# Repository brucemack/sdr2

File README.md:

Overview
========

This is a homebrew SDR rig with no dependency on external computers/soundcards/etc. 

Build/Debug Commands
====================

One-time setup of make process:

        git submodule update --init
        mkdir build
        cd build
        cmake -DPICO_BOARD=pico2 ..

Command used to flash code to board:        

        ~/git/openocd/src/openocd -s ~/git/openocd/tcl -f interface/cmsis-dap.cfg -f target/rp2350.cfg -c "adapter speed 5000" -c "rp2350.dap.core1 cortex_m reset_config sysresetreq" -c "program main.elf verify reset exit"

Pico 2 Pinout Notes
===================
```
GP0  - (Reserved for UART0 TX)
GP1  - (Reserved for UART0 RX)

GP2  - 
GP3  - 
GP4  - I2S SCK out to PCM1804 ADC and PCM5100 DAC
GP5  - RST out to PCM1804 ADC

GP6  - I2S DIN in from PC1804 ADC
GP7  - I2S BCK out to PC1804 ADC
GP8  - I2S LRCK out to PC1804 ADC
GP9  - I2S DOUT out to PCM5100 DAC

GP10 - I2S BCK out to PCM5100 DAC
GP11 - I2S LRCK out to PCM5100 DAC
GP12 - User button input 0
GP13 - User button input 1
GP14 - PTT input 
GP15 - 
GP16 - I2C0 SDA for Si5351 (Addr 0x60)
GP17 - I2C0 SCL for Si5351 (Addr 0x60)

GP18 - I2C1 SDA for display and IO expander
GP19 - I2C1 SCL for display and IO expander
GP20 - Rotary encoder I channel input
GP21 - Rotary encoder Q channel input

GP22 - 
GP26 - ADC0 for forward power
GP27 - ADC1 for reverse power
GP28 - 
```
IO Expander Notes
=================
```
P0 - User indicator LED output
P1 - Audio amplifier enable (Low=enable output, high=shutdown amplifier)
P2 - ADC Input Select (Low=Microphone preamp out, High=QSD channel out)
P3 - TX band select 0
P4 - TX band select 1
P5 - RX band select 0
P6 - RX band select 1
P7 - Transmit PA enable (active low)
```

Wiring Notes
============

* TXRX board I_PLUS (J4:1) -> Audio Breakout INL_PLUS (J4:1)
* TXRX board I_MINUS (J4:2) -> Audio Breakout INL_MINUS (J4:2)
* TXRX board Q_PLUS (J4:3) -> Audio Breakout INR_PLUS (J4:4)
* TXRX board Q_MINUS (J4:5) -> Audio Breakout INR_MINUS (J4:3)
* Microphone input is connected to the INL_PLUS/INL_MINUS pins on the audio breakout board.

Hardware Notes
==============

### Instrumentation Amplifiers on Receive Board

See Horowitz and Hill (3rd ed, section 5.16, figure 5.88) for a description of the 
instrumentation amplifier configuration used on the receive board.  Gain for this amplifier is 
controlled determined by 1 + 2 R<sub>f</sub> / R<sub>g</sub>.  Notice that the feedback 
path is tapped after a 47 ohm resistor to set the output impedance of the stage.

Assuming R<sub>f</sub> is 520, R<sub>g</sub> is 100, the theoretical gain is about 11.

### Random

dBm = 30 + 20 * log(Vrms/sqrt(Z0))

Research
========

Consider the PCM1863 ADC? 

Consider the TS5A4624 analog switch (logic high = 2.4V w/ 5V supply)

Consider PCF8574A IO expander: https://www.ti.com/lit/ds/symlink/pcf8574a.pdf?ts=1728869550852&ref_url=https%253A%252F%252Fwww.mouser.com%252F

RF Transistor: https://www.nxp.com/docs/en/data-sheet/BFU590G.pdf

References
==========

[PCM1804 Datasheet](https://www.ti.com/lit/ds/symlink/pcm1804.pdf)
[PCM5100 Datasheet](https://www.ti.com/lit/ds/symlink/pcm5102.pdf)

Steps to Build CMSIS-DSP
========================

The library gets built once in a parallel project:

        cd ~/pico
        mkdir CMSISDSP
        cd CMSISDSP
        git clone https://github.com/ARM-software/CMSIS-DSP.git        
        git clone https://github.com/ARM-software/CMSIS_6.git
        cp $PICO_SDK_PATH/external/pico_sdk_import.cmake .

Then setup the CMakeLists.txt shown below and build:

        mkdir build
        cd build
        # IMPORTANT! pico2 build enables the generation of FPU instructions
        cmake -DPICO_BOARD=pico2 ..
        make -j4

What the CMakeLists.txt looks like:

```
cmake_minimum_required (VERSION 3.6)

# Pull in Pico SDK (must be before project)
include(pico_sdk_import.cmake) 

set(HOME $ENV{HOME})
set(CMSISDSP ${HOME}/pico/CMSISDSP/CMSIS-DSP)
set(CMSISCORE ${HOME}/pico/CMSISDSP/CMSIS_6/CMSIS/Core)

# Define the project
project (cmsis-dsp VERSION 0.1)

# Initialise the Pico SDK
pico_sdk_init()

add_subdirectory(${CMSISDSP}/Source bin_dsp)

target_compile_options(CMSISDSP PUBLIC 
    -Wsign-compare
    -Wdouble-promotion
    -Ofast -ffast-math
    -DNDEBUG
    -Wall -Wextra  -Werror
    -fshort-enums 
    #-fshort-wchar
)
```

Example of referencing the built CMSIS-DSP library in a client project:

```
set(HOME $ENV{HOME})
target_include_directories(main PRIVATE
  ${HOME}/pico/CMSISDSP/CMSIS-DSP/Include
  ${HOME}/pico/CMSISDSP/CMSIS_6/CMSIS/Core/Include
)
target_link_libraries(main
  pico_stdlib
  ${HOME}/pico/CMSISDSP/build/bin_dsp/libCMSISDSP.a
)
```
License
=======

SDR2 Rig - Copyright (C) Bruce MacKinnon KC1FSZ, 2025

This program is free software: you can redistribute it and/or modify
it under the terms of the GNU General Public License as published by
the Free Software Foundation, either version 3 of the License, or
(at your option) any later version.

This program is distributed in the hope that it will be useful,
but WITHOUT ANY WARRANTY; without even the implied warranty of
MERCHANTABILITY or FITNESS FOR A PARTICULAR PURPOSE.  See the
GNU General Public License for more details.

You should have received a copy of the GNU General Public License
along with this program.  If not, see <https://www.gnu.org/licenses/>.

FOR AMATEUR RADIO USE ONLY.
NOT FOR COMMERCIAL USE WITHOUT PERMISSION.

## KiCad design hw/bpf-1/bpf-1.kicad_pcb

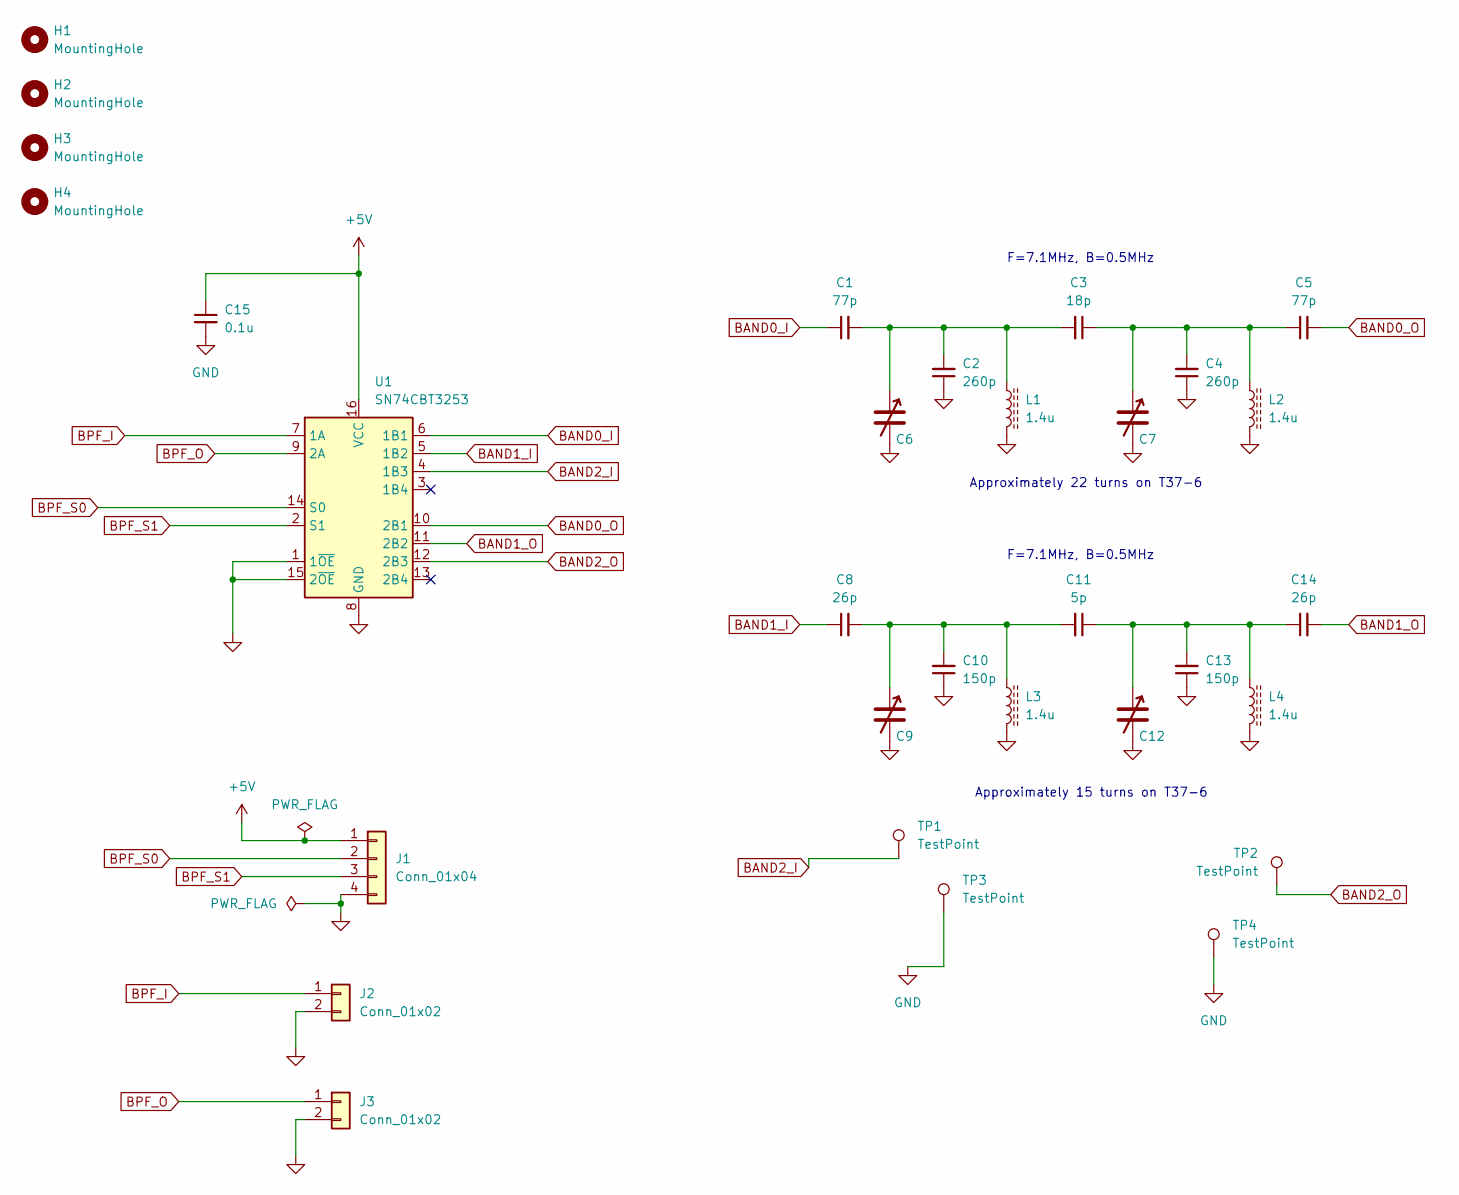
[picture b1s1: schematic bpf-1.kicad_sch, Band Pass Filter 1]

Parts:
C1, C5: 77p; C_0805_2012Metric_HandSolder
C2, C4: 260p; C_0805_2012Metric_HandSolder
C3: 18p; C_0805_2012Metric_HandSolder
C6, C7, C9, C12: C_Variable; VCAP_GKG30086-05_SGM-L
C8, C14: 26p; C_0805_2012Metric_HandSolder
C10, C13: 150p; C_0805_2012Metric_HandSolder
C11: 5p; C_0805_2012Metric_HandSolder
C15: 0.1u; C_0805_2012Metric_HandSolder
H1, H2, H3, H4: MountingHole; MountingHole_3.5mm
J1: Conn_01x04; PinHeader_1x04_P2.54mm_Vertical
J2, J3: Conn_01x02; PinHeader_1x02_P2.54mm_Vertical
L1, L2, L3, L4: 1.4u; FT37-43 Unifilar
TP1, TP2, TP3, TP4: TestPoint; TestPoint_Pad_1.5x1.5mm
U1: SN74CBT3253; SOIC-16_3.9x9.9mm_P1.27mm

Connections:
+5V: C15.1, J1.1, U1.16 (VCC)
BAND0_I: C1.1, U1.6 (1B1)
BAND0_O: C5.2, U1.10 (2B1)
BAND1_I: C8.1, U1.5 (1B2)
BAND1_O: C14.2, U1.11 (2B2)
BAND2_I: TP1.1, U1.4 (1B3)
BAND2_O: TP2.1, U1.12 (2B3)
BPF_I: J2.1, U1.7 (1A)
BPF_O: J3.1, U1.9 (2A)
BPF_S0: J1.2, U1.14 (S0)
BPF_S1: J1.3, U1.2 (S1)
GND: C2.1, C4.1, C6.2, C7.2, C9.2, C10.1, C12.2, C13.1, C15.2, J1.4, J2.2, J3.2, L1.2, L2.2, L3.2, L4.2, TP3.1, TP4.1, U1.1 (1~OE), U1.8 (GND), U1.15 (2~OE)
unnamed: C1.2, C2.2, C3.2, C6.1, L1.1
unnamed: C3.1, C4.2, C5.1, C7.1, L2.1
unnamed: C8.2, C9.1, C10.2, C11.2, L3.1
unnamed: C11.1, C12.1, C13.2, C14.1, L4.1

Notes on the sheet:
F=7.1MHz, B=0.5MHz
Approximately 15 turns on T37-6
Approximately 22 turns on T37-6

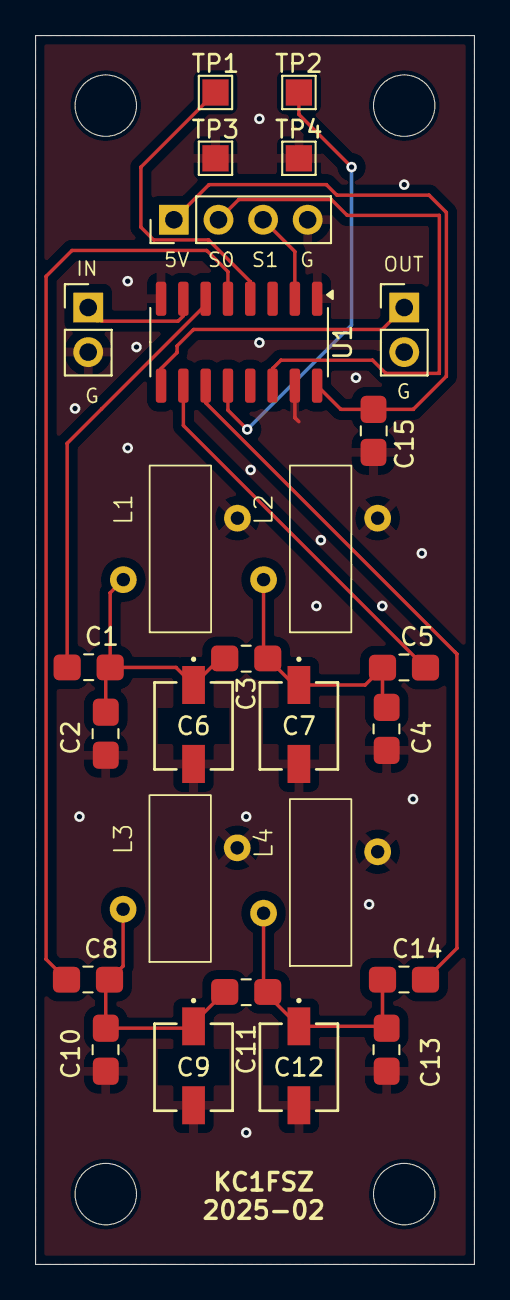
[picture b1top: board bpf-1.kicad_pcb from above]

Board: 2 copper layers, 25.0 x 70.0 mm, 31 parts (0 on the bottom side), 16 nets.

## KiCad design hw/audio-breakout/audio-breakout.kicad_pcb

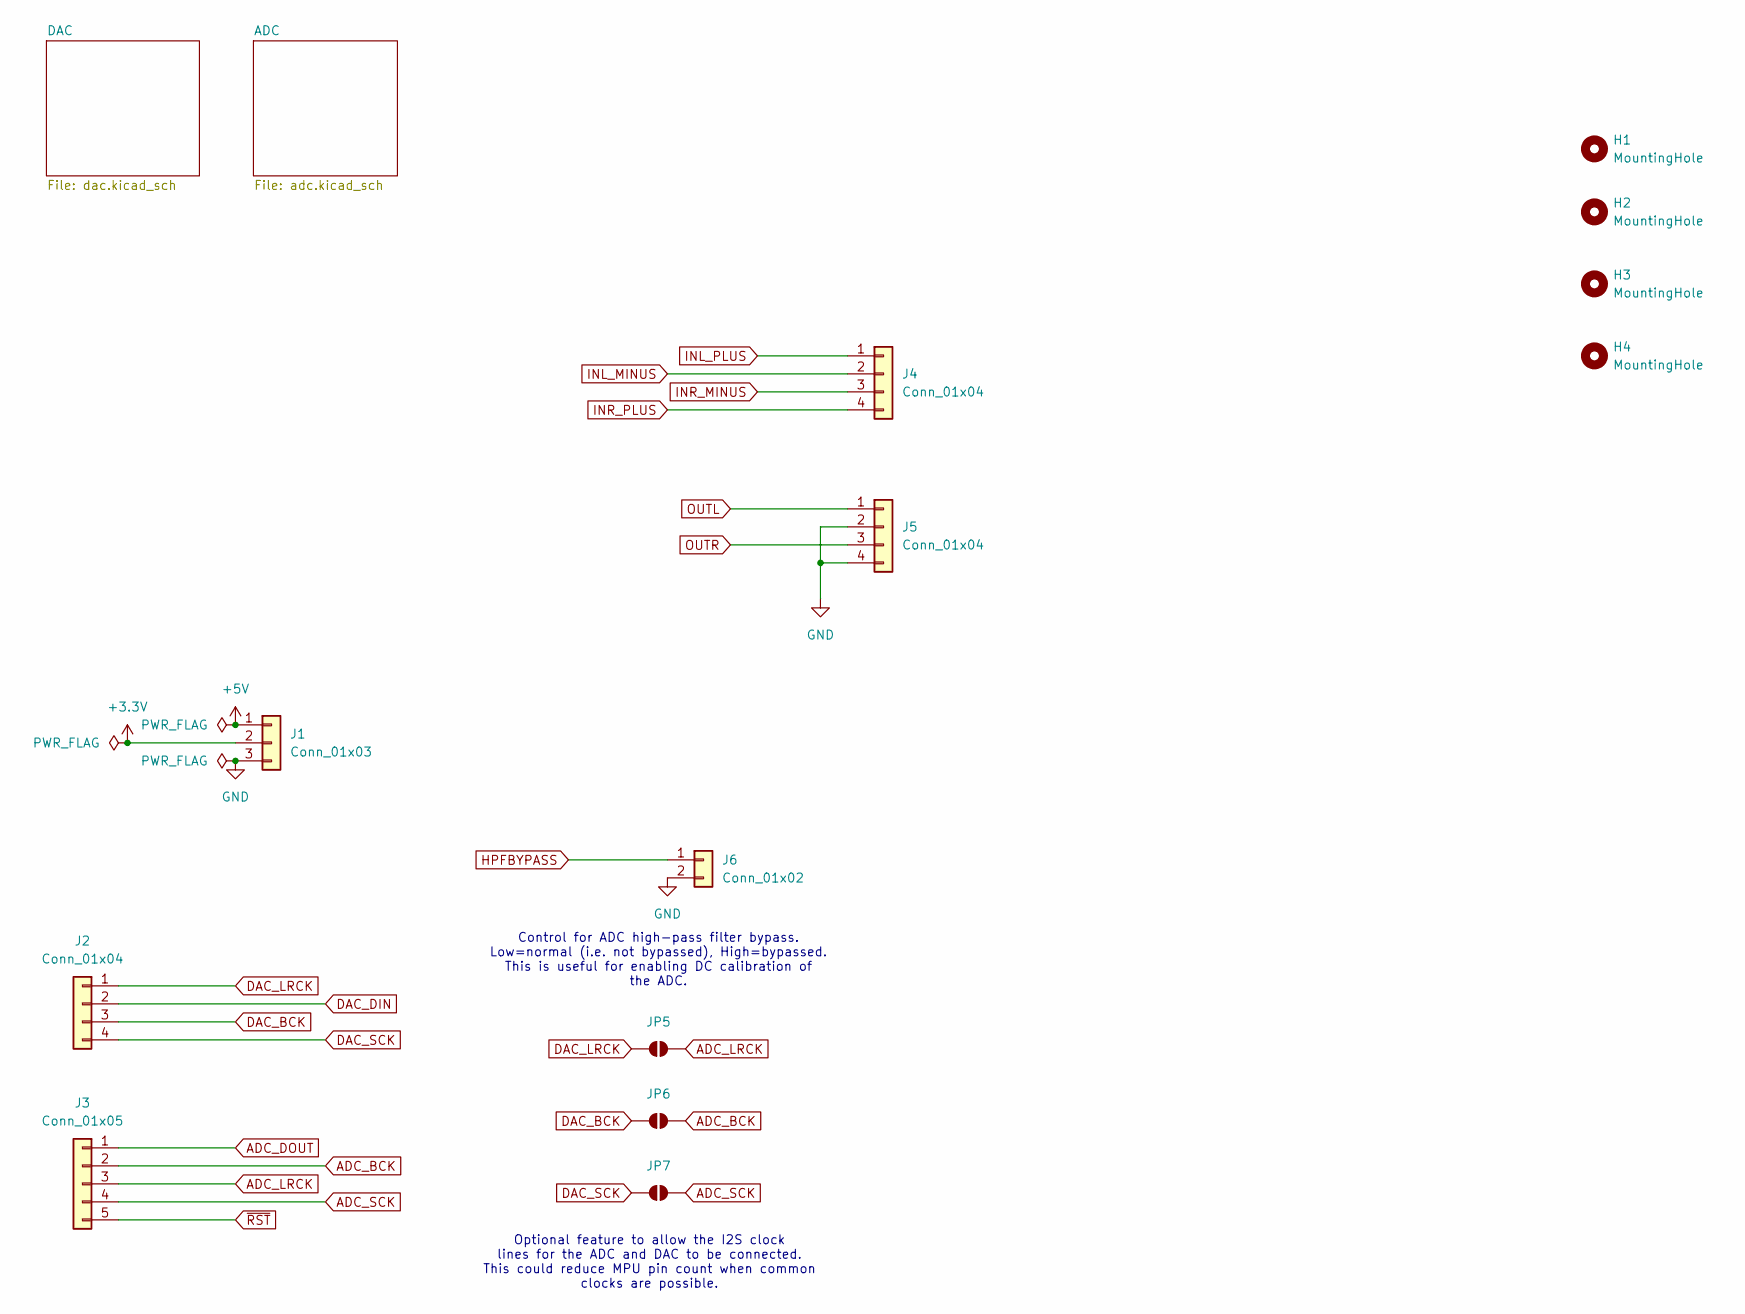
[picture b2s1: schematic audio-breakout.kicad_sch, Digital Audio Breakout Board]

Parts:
H1, H2, H3, H4: MountingHole; MountingHole_3.5mm
J1: Conn_01x03; PinSocket_1x03_P2.54mm_Vertical
J2: Conn_01x04; PinSocket_1x04_P2.54mm_Vertical
J3: Conn_01x05; PinSocket_1x05_P2.54mm_Vertical
J4, J5: Conn_01x04; PinHeader_1x04_P2.54mm_Vertical
J6: Conn_01x02
JP5, JP6, JP7: SolderJumper_2_Open; SolderJumper-2_P1.3mm_Open_Pad1.0x1.5mm

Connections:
+3.3V: J1.2; also elsewhere on the board
+5V: J1.1; also elsewhere on the board
ADC_BCK: J3.2, JP6.2 (B); also elsewhere on the board
ADC_DOUT: J3.1; also elsewhere on the board
ADC_LRCK: J3.3, JP5.2 (B); also elsewhere on the board
ADC_SCK: J3.4, JP7.2 (B); also elsewhere on the board
DAC_BCK: J2.3, JP6.1 (A); also elsewhere on the board
DAC_DIN: J2.2; also elsewhere on the board
DAC_LRCK: J2.1, JP5.1 (A); also elsewhere on the board
DAC_SCK: J2.4, JP7.1 (A); also elsewhere on the board
INL_MINUS: J4.2; also elsewhere on the board
INL_PLUS: J4.1; also elsewhere on the board
INR_MINUS: J4.3; also elsewhere on the board
INR_PLUS: J4.4; also elsewhere on the board
OUTL: J5.1; also elsewhere on the board
OUTR: J5.3; also elsewhere on the board
~RST: J3.5; also elsewhere on the board

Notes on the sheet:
Optional feature to allow the I2S clock lines for the ADC and DAC to be connected. This could reduce MPU pin count when common clocks are possible.
Control for ADC high-pass filter bypass. Low=normal (i.e. not bypassed), High=bypassed. This is useful for enabling DC calibration of the ADC.

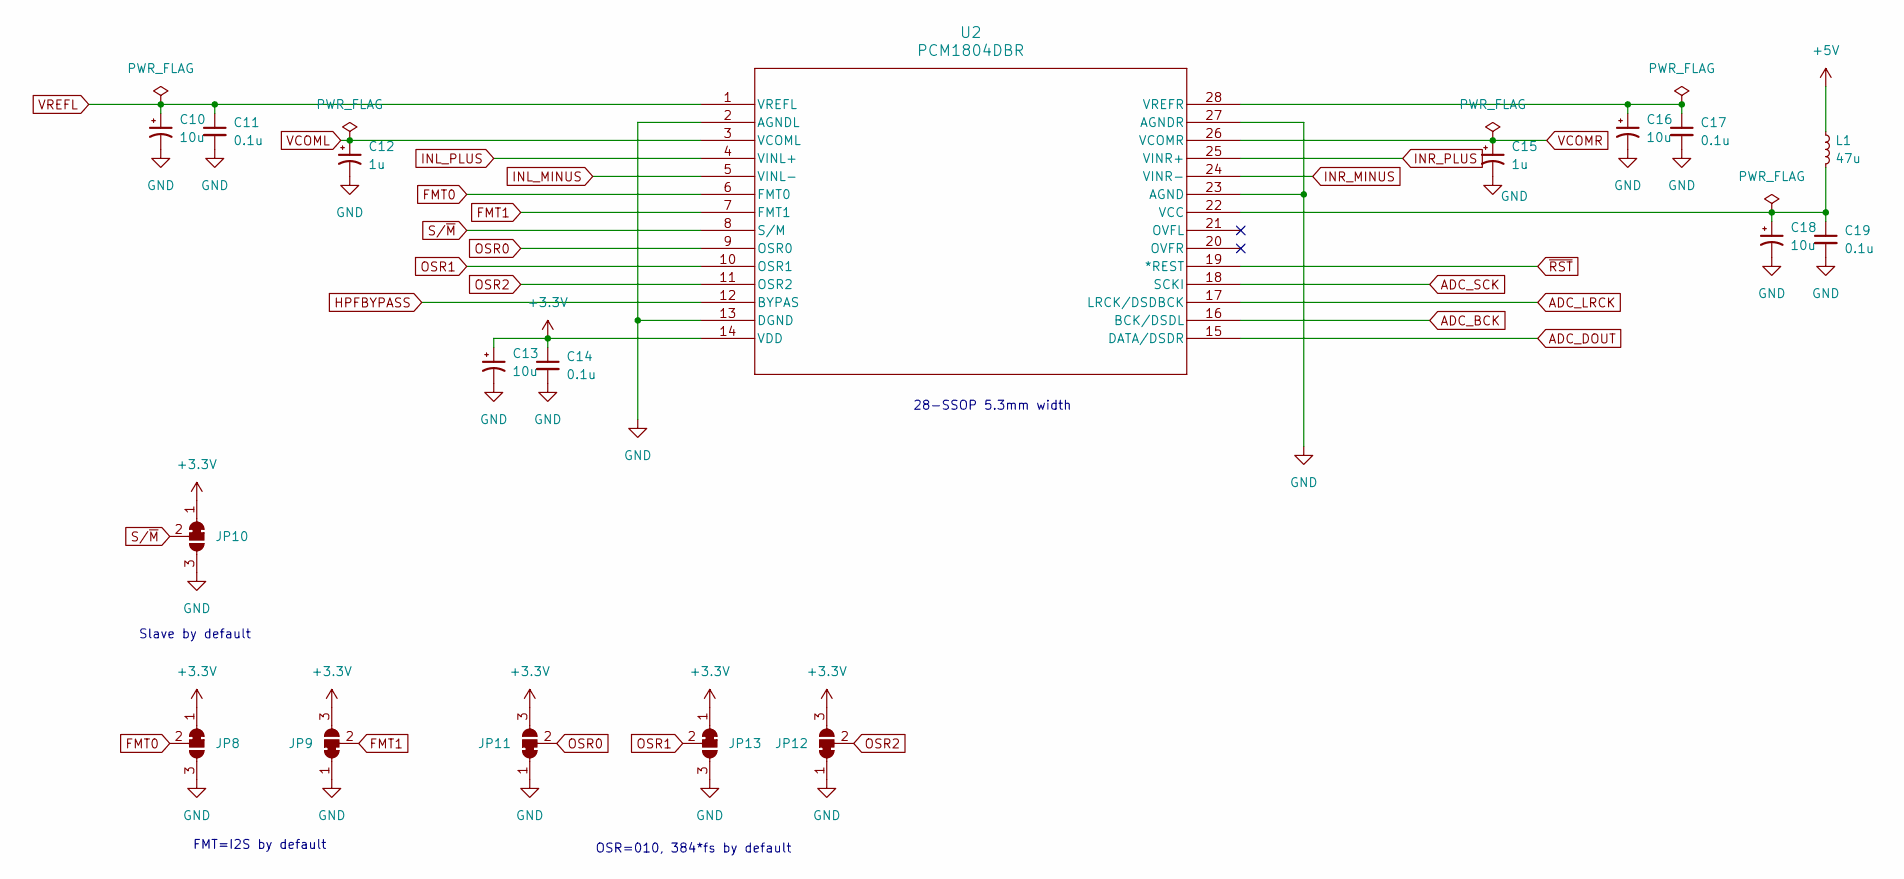
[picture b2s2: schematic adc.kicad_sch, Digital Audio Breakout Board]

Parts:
C10, C13, C16, C18: 10u; CP_Radial_D4.0mm_P2.00mm
C11, C14, C17, C19: 0.1u; C_0805_2012Metric_Pad1.18x1.45mm_HandSolder
C12, C15: 1u; C_0805_2012Metric_Pad1.18x1.45mm_HandSolder
JP8, JP9, JP10, JP11, JP12, JP13: SolderJumper_3_Bridged12; SolderJumper-3_P1.3mm_Bridged12_Pad1.0x1.5mm
L1: 47u; L_0805_2012Metric_Pad1.15x1.40mm_HandSolder
U2: PCM1804DBR; SSOP-28_5.3x10.2mm_P0.65mm

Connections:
+3.3V: C13.1, C14.1, JP8.1 (A), JP9.3 (B), JP10.1 (A), JP11.3 (B), JP12.3 (B), JP13.1 (A), U2.14 (VDD); also elsewhere on the board
+5V: L1.1; also elsewhere on the board
ADC_BCK: U2.16 (BCK/DSDL); also elsewhere on the board
ADC_DOUT: U2.15 (DATA/DSDR); also elsewhere on the board
ADC_LRCK: U2.17 (LRCK/DSDBCK); also elsewhere on the board
ADC_SCK: U2.18 (SCKI); also elsewhere on the board
FMT0: JP8.2 (C), U2.6 (FMT0)
FMT1: JP9.2 (C), U2.7 (FMT1)
INL_MINUS: U2.5 (VINL-); also elsewhere on the board
INL_PLUS: U2.4 (VINL+); also elsewhere on the board
INR_MINUS: U2.24 (VINR-); also elsewhere on the board
INR_PLUS: U2.25 (VINR+); also elsewhere on the board
unnamed: C18.1, C19.1, L1.2, U2.22 (VCC)
unnamed: C16.1, C17.1, U2.28 (VREFR)
OSR0: JP11.2 (C), U2.9 (OSR0)
OSR1: JP13.2 (C), U2.10 (OSR1)
OSR2: JP12.2 (C), U2.11 (OSR2)
S/~M: JP10.2 (C), U2.8 (S/M)
VCOML: C12.1, U2.3 (VCOML)
VCOMR: C15.1, U2.26 (VCOMR)
VREFL: C10.1, C11.1, U2.1 (VREFL)
~RST: U2.19 (*REST); also elsewhere on the board

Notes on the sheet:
FMT=I2S by default
Slave by default
OSR=010, 384*fs by default
28-SSOP 5.3mm width

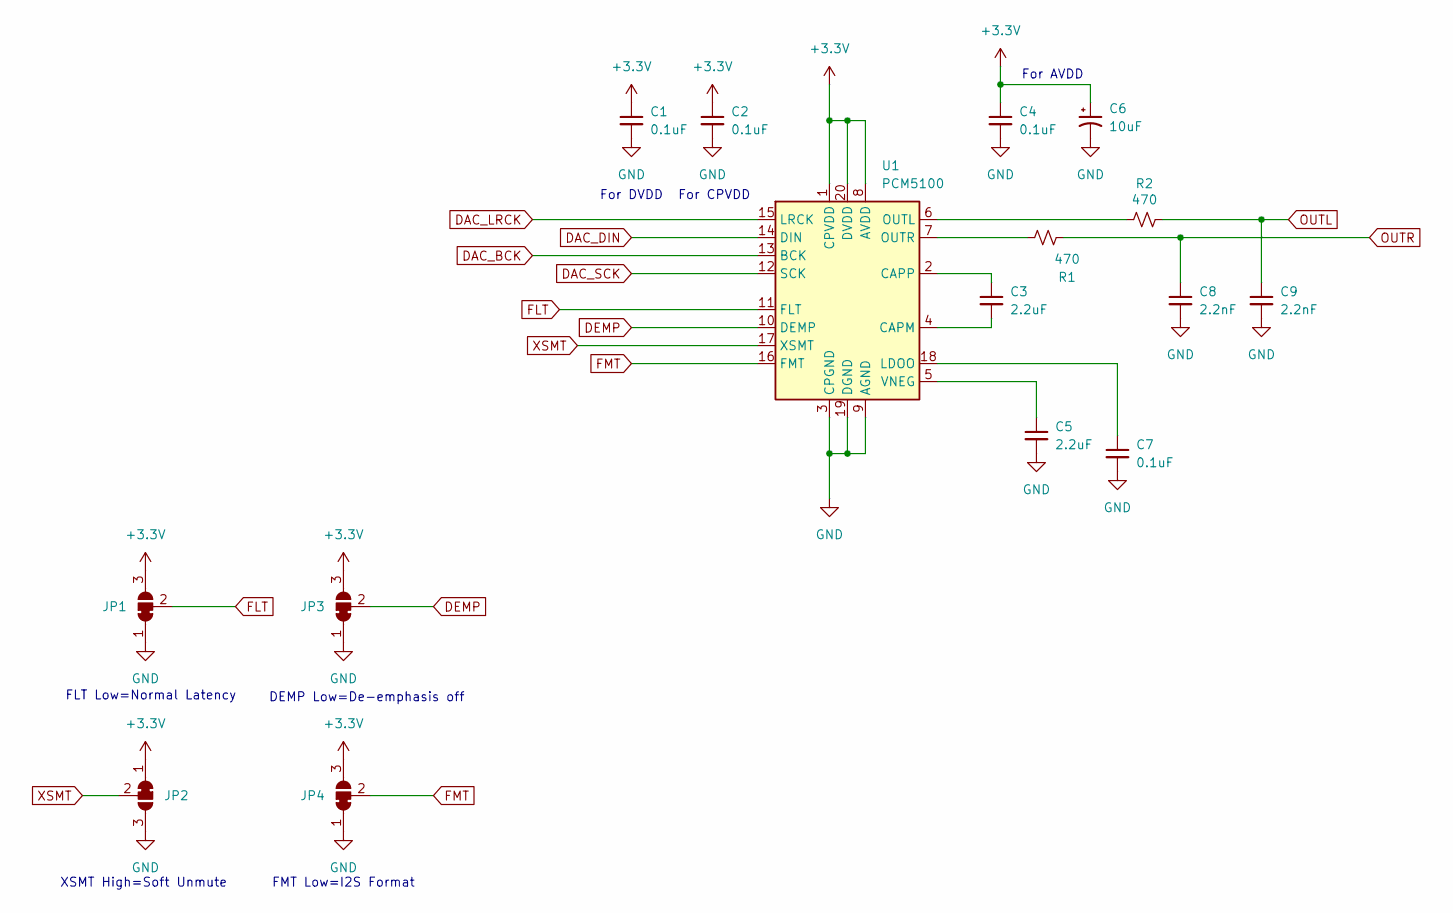
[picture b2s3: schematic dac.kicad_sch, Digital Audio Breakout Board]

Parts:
C1, C2, C4, C7: 0.1uF; C_0805_2012Metric_Pad1.18x1.45mm_HandSolder
C3, C5: 2.2uF; C_0805_2012Metric_Pad1.18x1.45mm_HandSolder
C6: 10uF; CP_Radial_D4.0mm_P2.00mm
C8, C9: 2.2nF; C_0805_2012Metric_Pad1.18x1.45mm_HandSolder
JP1, JP2, JP3, JP4: SolderJumper_3_Bridged12; SolderJumper-3_P1.3mm_Bridged12_Pad1.0x1.5mm
R1, R2: 470; R_0805_2012Metric_Pad1.20x1.40mm_HandSolder
U1: PCM5100; TSSOP-20_4.4x6.5mm_P0.65mm

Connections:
+3.3V: C1.1, C2.1, C4.1, C6.1, JP1.3 (B), JP2.1 (A), JP3.3 (B), JP4.3 (B), U1.1 (CPVDD), U1.8 (AVDD), U1.20 (DVDD); also elsewhere on the board
DAC_BCK: U1.13 (BCK); also elsewhere on the board
DAC_DIN: U1.14 (DIN); also elsewhere on the board
DAC_LRCK: U1.15 (LRCK); also elsewhere on the board
DAC_SCK: U1.12 (SCK); also elsewhere on the board
DEMP: JP3.2 (C), U1.10 (DEMP)
FLT: JP1.2 (C), U1.11 (FLT)
FMT: JP4.2 (C), U1.16 (FMT)
unnamed: C3.2, U1.4 (CAPM)
unnamed: C3.1, U1.2 (CAPP)
unnamed: C7.1, U1.18 (LDOO)
unnamed: R2.2, U1.6 (OUTL)
unnamed: R1.2, U1.7 (OUTR)
unnamed: C5.1, U1.5 (VNEG)
OUTL: C9.1, R2.1; also elsewhere on the board
OUTR: C8.1, R1.1; also elsewhere on the board
XSMT: JP2.2 (C), U1.17 (XSMT)

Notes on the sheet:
FLT Low=Normal Latency
For CPVDD
For DVDD
DEMP Low=De-emphasis off
XSMT High=Soft Unmute
For AVDD
FMT Low=I2S Format

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
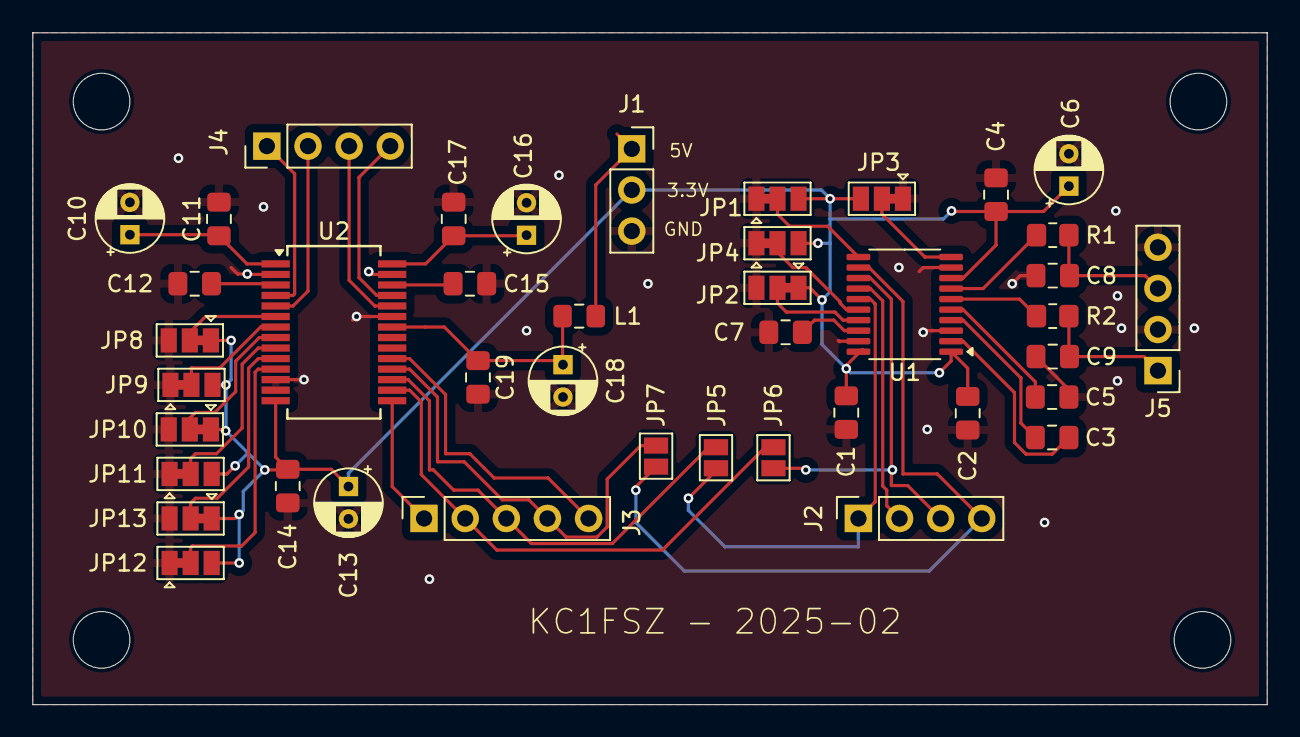
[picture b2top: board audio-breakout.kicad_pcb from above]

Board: 2 copper layers, 76.2 x 41.5 mm, 46 parts (0 on the bottom side), 39 nets.

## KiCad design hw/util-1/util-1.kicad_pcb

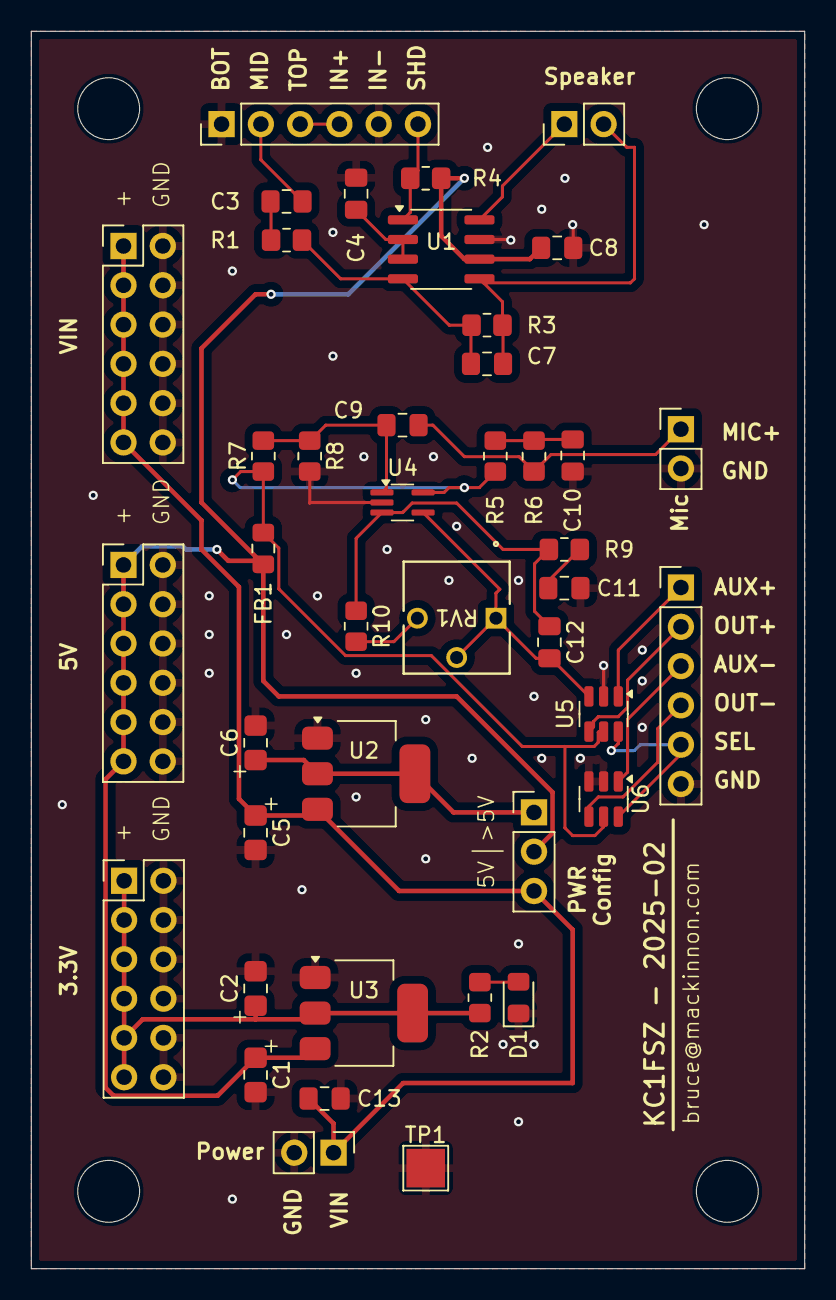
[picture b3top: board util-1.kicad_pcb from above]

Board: 2 copper layers, 50.0 x 80.0 mm, 46 parts (0 on the bottom side), 27 nets.

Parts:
C1, C2, C5, C6: 10u; CPOL_0805_2012Metric_Pad1.18x1.45mm_HandSolder
C3: 0.39uF; C_0805_2012Metric_Pad1.18x1.45mm_HandSolder
C4: 1.0uF; C_0805_2012Metric_Pad1.18x1.45mm_HandSolder
C7: NC; C_0805_2012Metric_Pad1.18x1.45mm_HandSolder
C8, C10, C13: 0.1uF; C_0805_2012Metric_Pad1.18x1.45mm_HandSolder
C9: 0.01uF; C_0805_2012Metric_Pad1.18x1.45mm_HandSolder
C11: 10uF; C_0805_2012Metric_Pad1.18x1.45mm_HandSolder
C12: 100pF; C_0805_2012Metric_Pad1.18x1.45mm_HandSolder
D1: Red; LED_0805_2012Metric_Pad1.15x1.40mm_HandSolder
FB1: FerriteBead; L_0805_2012Metric_Pad1.15x1.40mm_HandSolder
H1, H2, H3, H4: MountingHole; MountingHole_4mm
J1, J4, J6: Conn_01x02; PinHeader_1x02_P2.54mm_Vertical
J2: Conn_01x03; PinHeader_1x03_P2.54mm_Vertical
J3, J5: Conn_01x06; PinHeader_1x06_P2.54mm_Vertical
J7: 5V; PinHeader_2x06_P2.54mm_Vertical
J8: 3.3V; PinHeader_2x06_P2.54mm_Vertical
J9: BATT; PinHeader_2x06_P2.54mm_Vertical
R1, R3: 20k; R_0805_2012Metric_Pad1.20x1.40mm_HandSolder
R2: 100; R_0805_2012Metric_Pad1.20x1.40mm_HandSolder
R4, R5, R6, R9: 1k; R_0805_2012Metric_Pad1.20x1.40mm_HandSolder
R7, R8: 1M; R_0805_2012Metric_Pad1.20x1.40mm_HandSolder
R10: 22k; R_0805_2012Metric_Pad1.20x1.40mm_HandSolder
RV1: 100k; POT_3362P
TP1: TestPoint; TestPoint_Pad_2.5x2.5mm
U1: SOIC-8_3.9x4.9mm_P1.27mm
U2: NCP1117-5.0_SOT223; SOT-223-3_TabPin2
U3: NCP1117-3.3_SOT223; SOT-223-3_TabPin2
U4: MAX4466EXK; SOT-353_SC-70-5_Handsoldering
U5, U6: TS5A3159ADBVR; SOT-23-6

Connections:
+3V3: C2.1, J8.1, J8.3, J8.5, J8.7, J8.9, J8.11, R2.1, U3.2 (VO)
+5V: C1.1, C8.1, FB1.1, J2.2, J7.1, J7.3, J7.5, J7.7, J7.9, J7.11, R4.1, U1.6 (VDD), U3.3 (VI)
+5VA: FB1.2, R5.1, R7.1, U4.5 (VCC), U5.5 (V+), U6.5 (V+)
+BATT: C5.1, C13.1, J1.1, J2.3, J9.1, J9.3, J9.5, J9.7, J9.9, J9.11, U2.3 (VI)
AI_OUT: C12.2, RV1.1, RV1.2, U4.4 (OUT), U5.3
AUX+: J3.1, U5.1
AUX-: J3.3, U6.1
AUX_SEL: J3.5, U5.6, U6.6
GND: C1.2, C2.2, C4.2, C5.2, C6.2, C8.2, C10.1, C11.1, C13.2, D1.1 (K), J1.2, J3.6, J5.1, J5.5, J6.2, J7.2, J7.4, J7.6, J7.8, J7.10, J7.12, J8.2, J8.4, J8.6, J8.8, J8.10, J8.12, J9.2, J9.4, J9.6, J9.8, J9.10, J9.12, R8.2, TP1.1, U1.7 (GND), U2.1 (GND), U3.1 (GND), U4.2 (GND), U5.2 (GND), U6.2 (GND), U6.3
unnamed: C3.2, R1.1
unnamed: C10.2, R5.2, R6.1
unnamed: C11.2, R9.2
unnamed: D1.2 (A), R2.2
unnamed: C6.1, J2.1, U2.2 (VO)
unnamed: J4.1, U1.8 (Vo2)
unnamed: C7.1, J4.2, R3.2, U1.5 (Vo1)
unnamed: C3.1, J5.2
unnamed: J5.3, J5.4
unnamed: J5.6, R4.2, U1.1 (SHUTDOWN)
unnamed: C9.1, J6.1, R6.2
unnamed: R10.2, RV1.3
unnamed: C4.1, U1.2 (BYPASS), U1.3 (+IN)
unnamed: C7.2, R1.2, R3.1, U1.4 (-IN)
unnamed: C9.2, R7.2, R8.1, U4.1 (IN+)
unnamed: C12.1, R9.1, R10.1, U4.3 (IN-)
OUT+: J3.2, U5.4
OUT-: J3.4, U6.4

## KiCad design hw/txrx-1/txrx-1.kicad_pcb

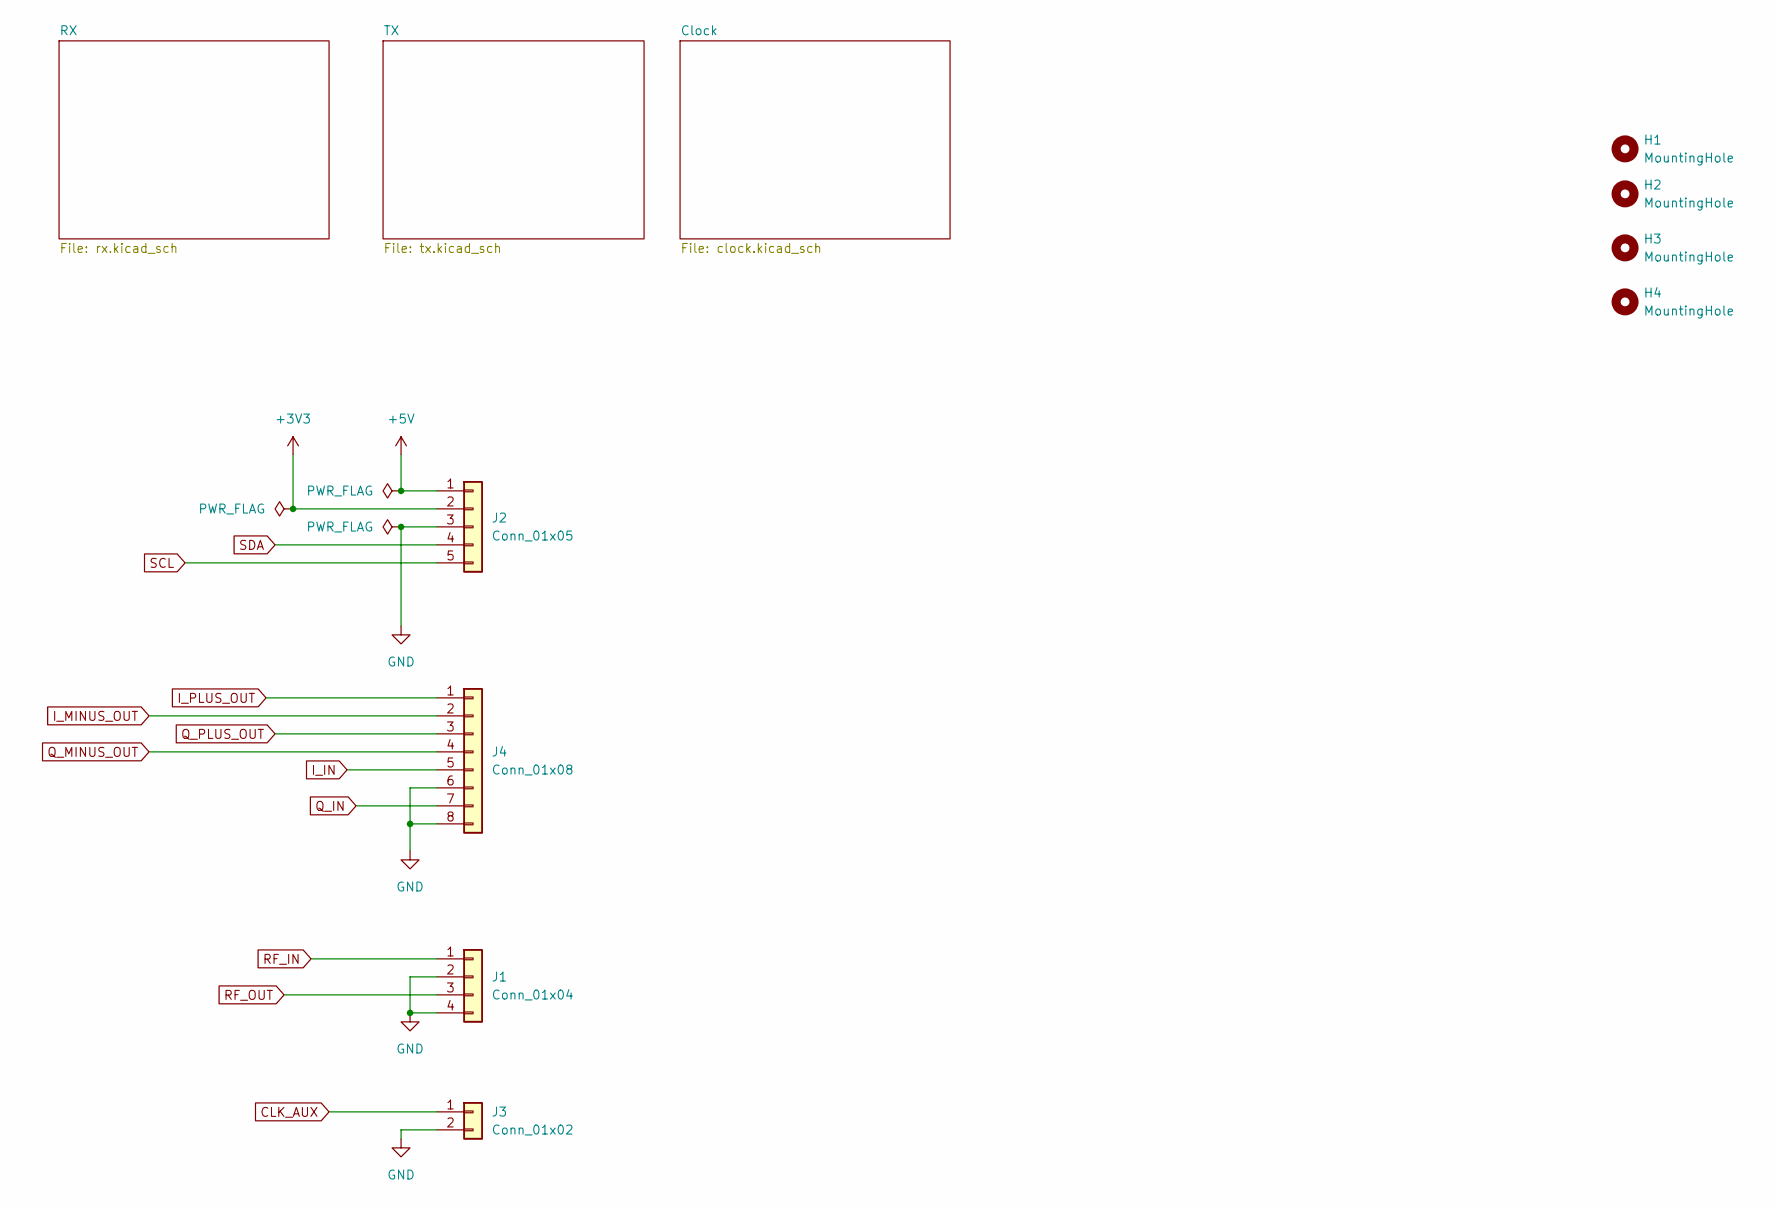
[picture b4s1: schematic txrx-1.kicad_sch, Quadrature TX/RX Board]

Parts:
H1, H2, H3, H4: MountingHole; MountingHole_3.5mm
J1: Conn_01x04; PinHeader_1x04_P2.54mm_Vertical
J2: Conn_01x05; PinHeader_1x05_P2.54mm_Vertical
J3: Conn_01x02; PinHeader_1x02_P2.54mm_Vertical
J4: Conn_01x08; PinHeader_1x08_P2.54mm_Vertical

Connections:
+3V3: J2.2; also elsewhere on the board
+5V: J2.1; also elsewhere on the board
CLK_AUX: J3.1; also elsewhere on the board
GND: J1.2, J1.4, J2.3, J3.2, J4.6, J4.8; also elsewhere on the board
I_IN: J4.5; also elsewhere on the board
I_MINUS_OUT: J4.2; also elsewhere on the board
I_PLUS_OUT: J4.1; also elsewhere on the board
Q_IN: J4.7; also elsewhere on the board
Q_MINUS_OUT: J4.4; also elsewhere on the board
Q_PLUS_OUT: J4.3; also elsewhere on the board
RF_IN: J1.1; also elsewhere on the board
RF_OUT: J1.3; also elsewhere on the board
SCL: J2.5; also elsewhere on the board
SDA: J2.4; also elsewhere on the board

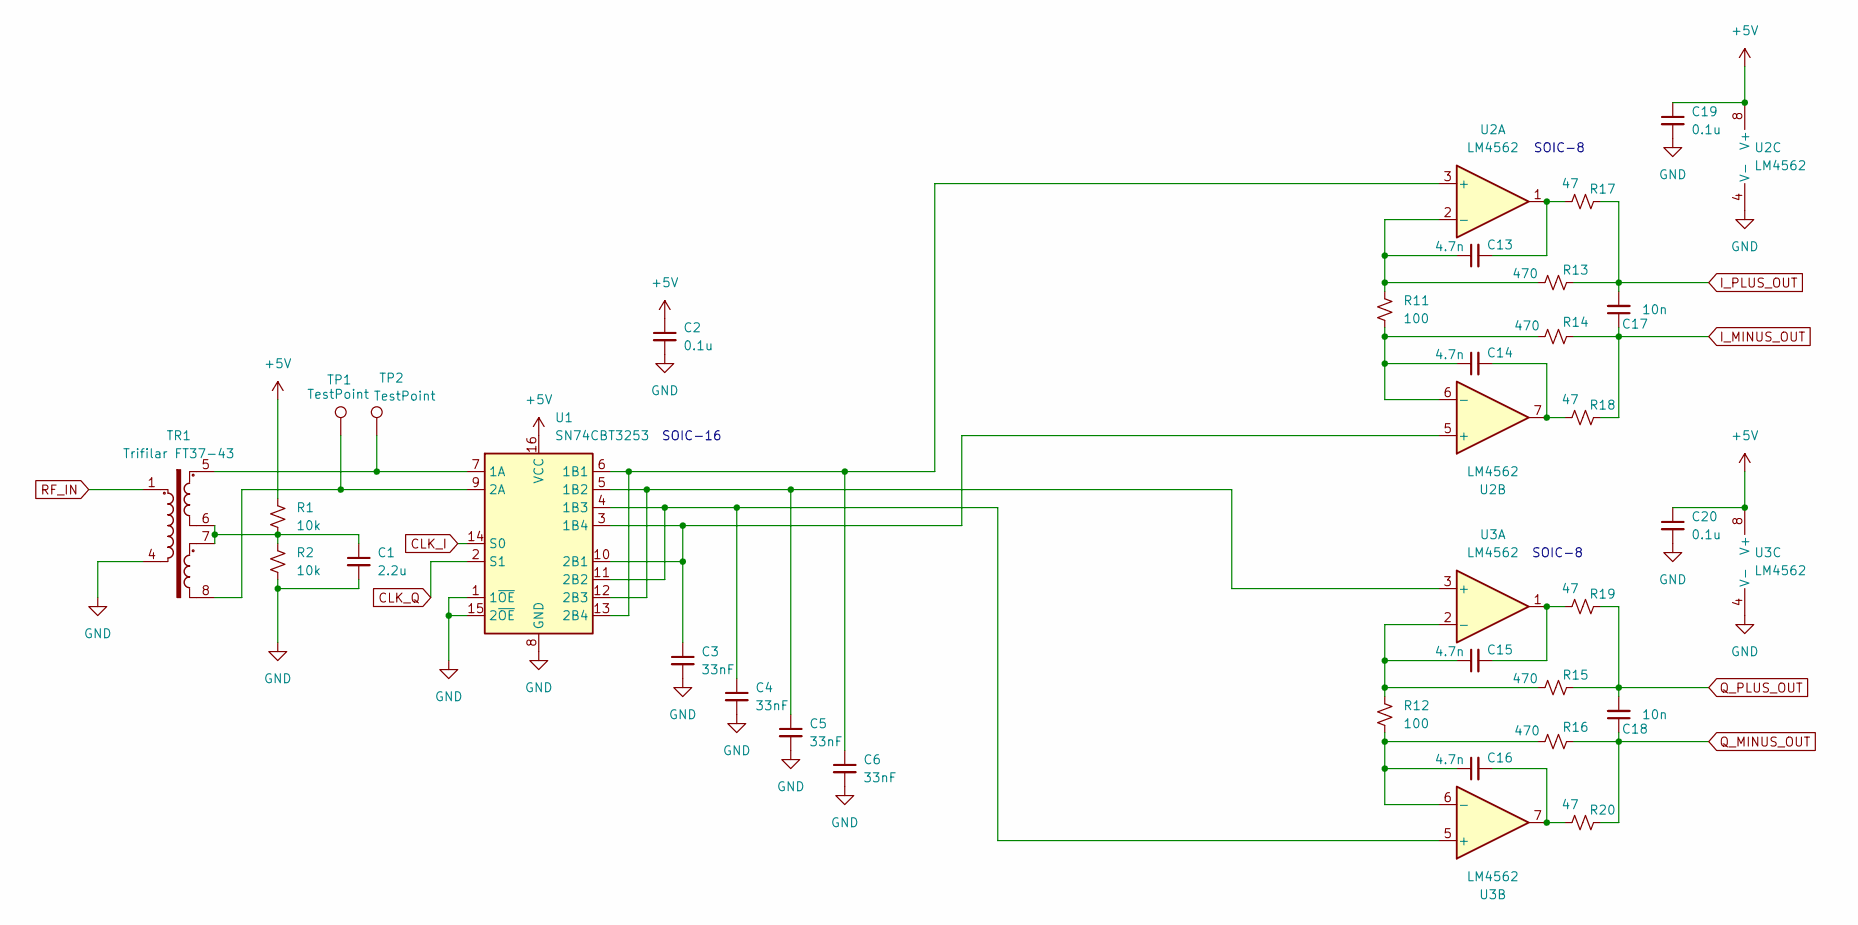
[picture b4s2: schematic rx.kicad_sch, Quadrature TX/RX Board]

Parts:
C1: 2.2u; C_0805_2012Metric_Pad1.18x1.45mm_HandSolder
C2, C19, C20: 0.1u; C_0805_2012Metric_Pad1.18x1.45mm_HandSolder
C3, C4, C5, C6: 33nF; C_0805_2012Metric_Pad1.18x1.45mm_HandSolder
C13, C14, C15, C16: 4.7n; C_0805_2012Metric_Pad1.18x1.45mm_HandSolder
C17, C18: 10n; C_0805_2012Metric_Pad1.18x1.45mm_HandSolder
R1, R2: 10k; R_0805_2012Metric_Pad1.20x1.40mm_HandSolder
R11, R12: 100; R_0805_2012Metric_Pad1.20x1.40mm_HandSolder
R13, R14, R15, R16: 470; R_0805_2012Metric_Pad1.20x1.40mm_HandSolder
R17, R18, R19, R20: 47; R_0805_2012Metric_Pad1.20x1.40mm_HandSolder
TP1, TP2: TestPoint; TestPoint_Pad_1.5x1.5mm
TR1: Trifilar FT37-43; FT37-43 Trifilar
U1: SN74CBT3253; SOIC-16_3.9x9.9mm_P1.27mm
U2, U3: LM4562; SOIC-8_3.9x4.9mm_P1.27mm

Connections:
+5V: C2.1, C19.1, C20.1, R1.1, U1.16 (VCC), U2.8 (V+), U3.8 (V+); also elsewhere on the board
CLK_I: U1.14 (S0); also elsewhere on the board
CLK_Q: U1.2 (S1); also elsewhere on the board
GND: C1.2, C2.2, C3.2, C4.2, C5.2, C6.2, C19.2, C20.2, R2.2, TR1.4, U1.1 (1~OE), U1.8 (GND), U1.15 (2~OE), U2.4 (V-), U3.4 (V-); also elsewhere on the board
I_MINUS_OUT: C17.1, R14.2, R18.2; also elsewhere on the board
I_PLUS_OUT: C17.2, R13.2, R17.2; also elsewhere on the board
unnamed: C1.1, R1.2, R2.1, TR1.6, TR1.7
unnamed: C13.2, R17.1, U2.1
unnamed: C14.2, R18.1, U2.7
unnamed: C15.2, R19.1, U3.1
unnamed: C16.2, R20.1, U3.7
unnamed: TP2.1, TR1.5, U1.7 (1A)
unnamed: C6.1, U1.6 (1B1), U1.13 (2B4), U2.3 (+)
unnamed: C5.1, U1.5 (1B2), U1.12 (2B3), U3.3 (+)
unnamed: C4.1, U1.4 (1B3), U1.11 (2B2), U3.5 (+)
unnamed: C3.1, U1.3 (1B4), U1.10 (2B1), U2.5 (+)
unnamed: TP1.1, TR1.8, U1.9 (2A)
unnamed: C13.1, R11.1, R13.1, U2.2 (-)
unnamed: C14.1, R11.2, R14.1, U2.6 (-)
unnamed: C15.1, R12.1, R15.1, U3.2 (-)
unnamed: C16.1, R12.2, R16.1, U3.6 (-)
Q_MINUS_OUT: C18.1, R16.2, R20.2; also elsewhere on the board
Q_PLUS_OUT: C18.2, R15.2, R19.2; also elsewhere on the board
RF_IN: TR1.1; also elsewhere on the board

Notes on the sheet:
SOIC-8
SOIC-16

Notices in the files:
hw/audio-breakout/adc.kicad_sch:
Copyright (C) 2025
hw/bpf-1/bpf-1.kicad_pcb:
Copyright (C) Bruce MacKinnon, 2025
